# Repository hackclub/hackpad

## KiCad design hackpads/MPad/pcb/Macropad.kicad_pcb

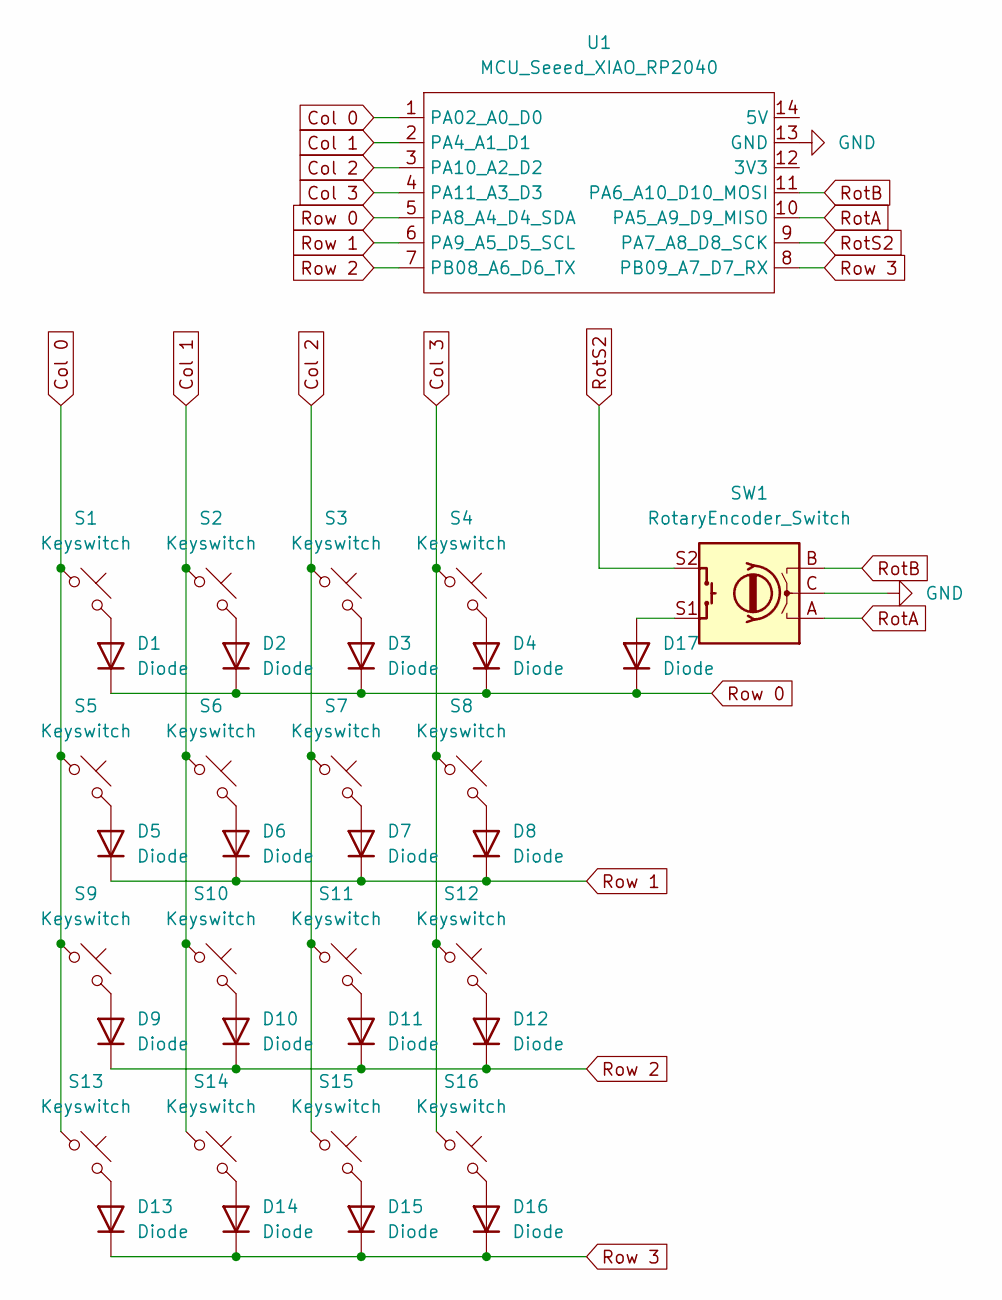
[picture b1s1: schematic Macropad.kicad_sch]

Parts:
D1, D2, D3, D4, D5, D6, D7, D8, D9, D10, D11, D12, D13, D14, D15, D16, D17: Diode; Diode_DO-35
S1, S2, S3, S4, S5, S6, S7, S8, S9, S10, S11, S12, S13, S14, S15, S16: Keyswitch; MX_PCB_1.00u
SW1: RotaryEncoder_Switch; RotaryEncoder_Alps_EC11E-Switch_Vertical_H20mm_CircularMoun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
U1: MCU_Seeed_XIAO_RP2040; Seeed_XIAO_RP2040

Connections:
Col 0: S1.1, S5.1, S9.1, S13.1, U1.1 (PA02_A0_D0)
Col 1: S2.1, S6.1, S10.1, S14.1, U1.2 (PA4_A1_D1)
Col 2: S3.1, S7.1, S11.1, S15.1, U1.3 (PA10_A2_D2)
Col 3: S4.1, S8.1, S12.1, S16.1, U1.4 (PA11_A3_D3)
GND: SW1.C, U1.13 (GND)
unnamed: D1.2 (A), S1.2
unnamed: D2.2 (A), S2.2
unnamed: D3.2 (A), S3.2
unnamed: D4.2 (A), S4.2
unnamed: D5.2 (A), S5.2
unnamed: D6.2 (A), S6.2
unnamed: D7.2 (A), S7.2
unnamed: D8.2 (A), S8.2
unnamed: D9.2 (A), S9.2
unnamed: D10.2 (A), S10.2
unnamed: D11.2 (A), S11.2
unnamed: D12.2 (A), S12.2
unnamed: D13.2 (A), S13.2
unnamed: D14.2 (A), S14.2
unnamed: D15.2 (A), S15.2
unnamed: D16.2 (A), S16.2
unnamed: D17.2 (A), SW1.S1
RotA: SW1.A, U1.10 (PA5_A9_D9_MISO)
RotB: SW1.B, U1.11 (PA6_A10_D10_MOSI)
RotS2: SW1.S2, U1.9 (PA7_A8_D8_SCK)
Row 0: D1.1 (K), D2.1 (K), D3.1 (K), D4.1 (K), D17.1 (K), U1.5 (PA8_A4_D4_SDA)
Row 1: D5.1 (K), D6.1 (K), D7.1 (K), D8.1 (K), U1.6 (PA9_A5_D5_SCL)
Row 2: D9.1 (K), D10.1 (K), D11.1 (K), D12.1 (K), U1.7 (PB08_A6_D6_TX)
Row 3: D13.1 (K), D14.1 (K), D15.1 (K), D16.1 (K), U1.8 (PB09_A7_D7_RX)

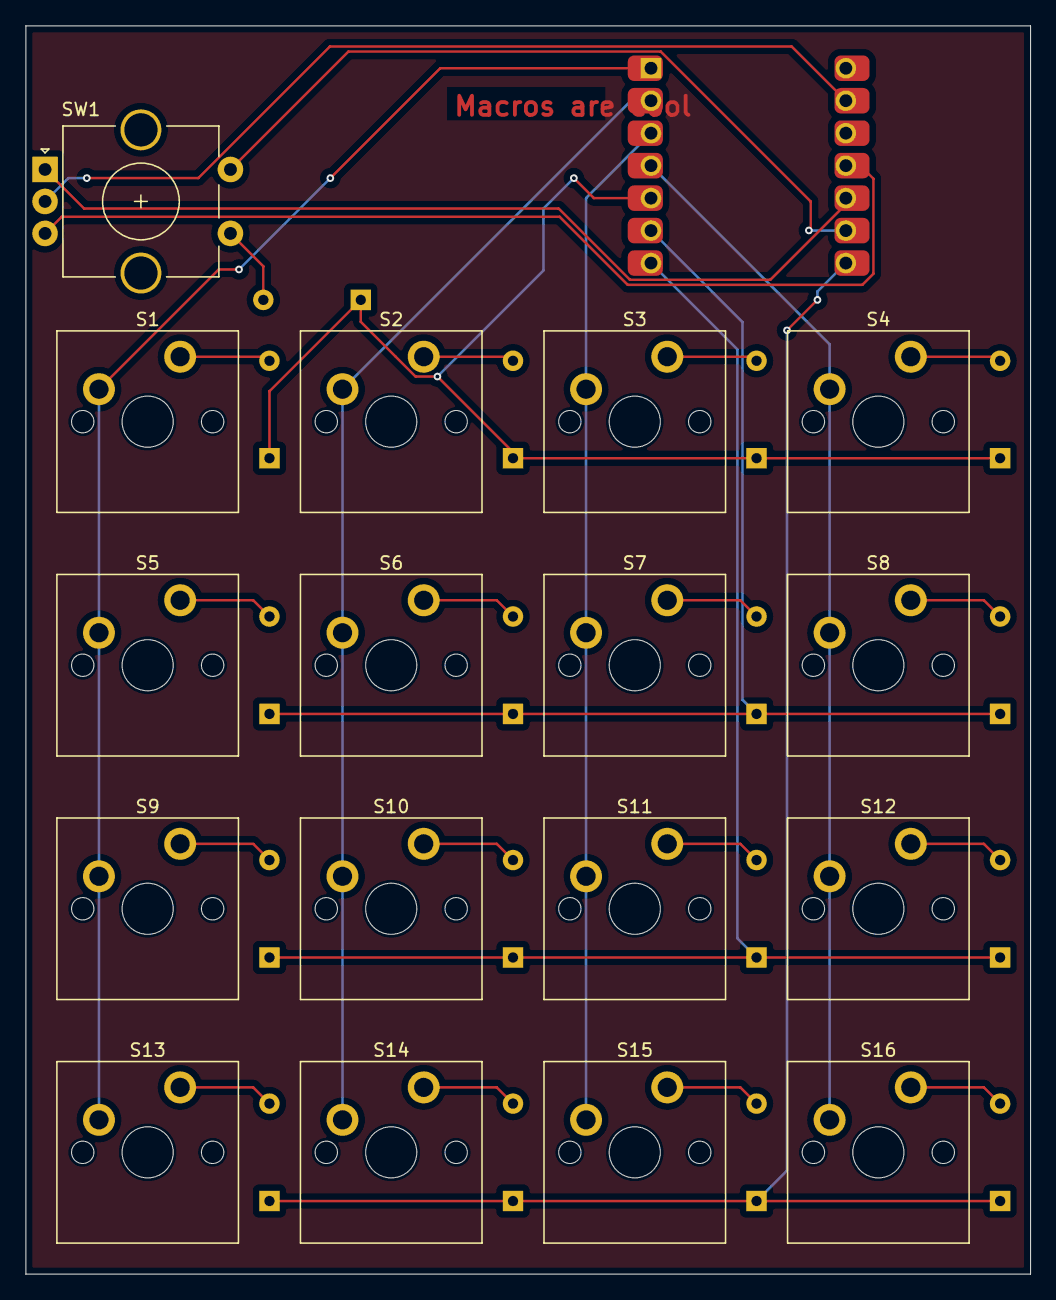
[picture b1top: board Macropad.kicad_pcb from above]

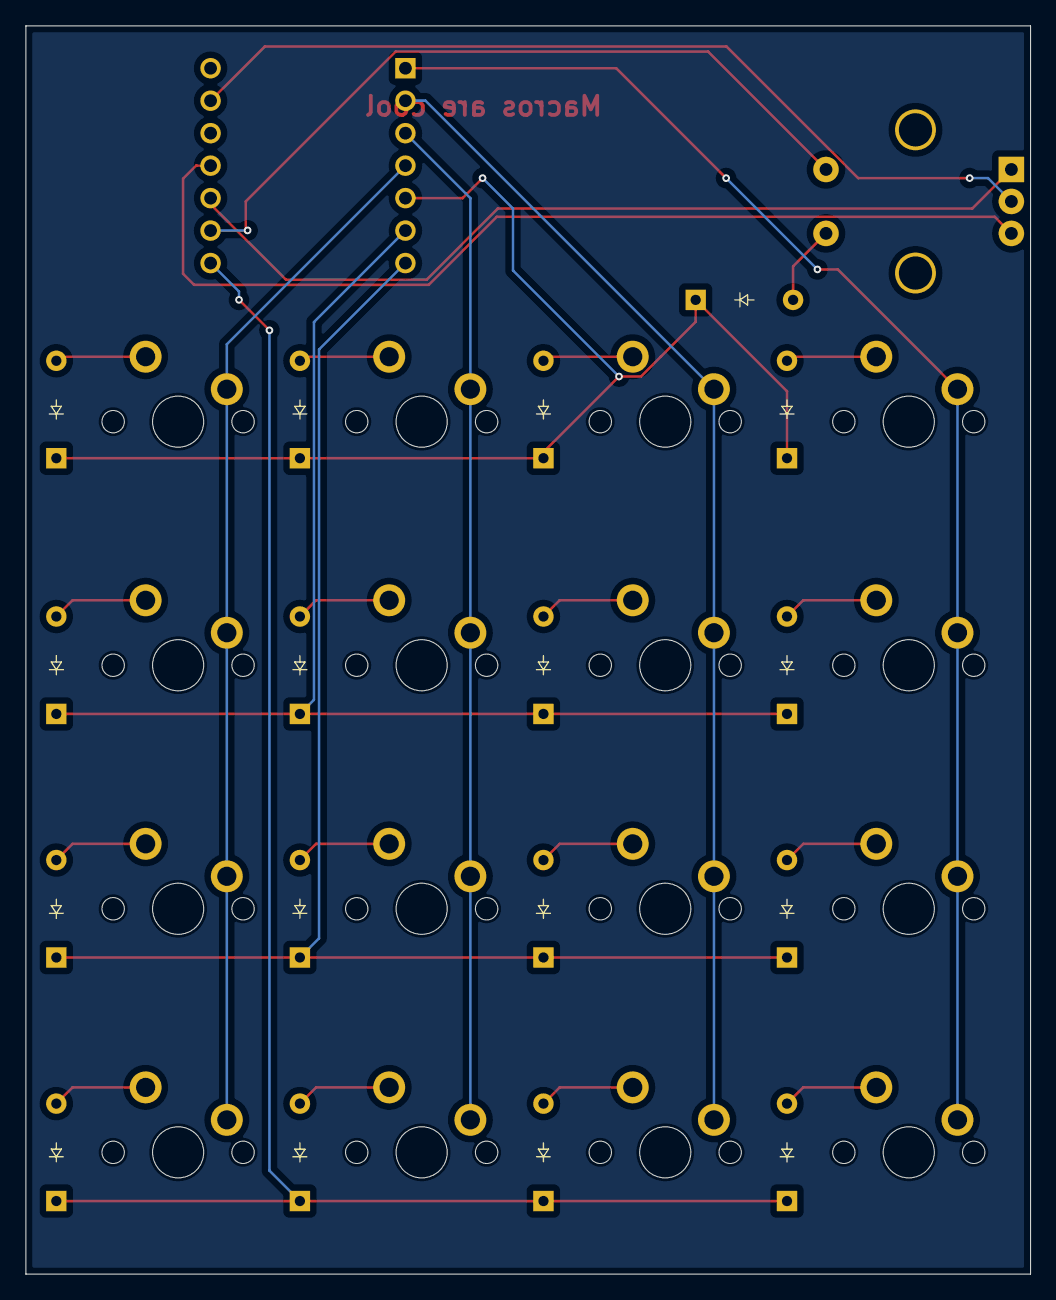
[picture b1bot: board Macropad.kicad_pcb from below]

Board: 2 copper layers, 78.6 x 97.6 mm, 35 parts (17 on the bottom side), 29 nets.

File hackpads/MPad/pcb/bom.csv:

Designator,Footprint,Quantity,Value,LCSC Part #
"D1, D10, D11, D12, D13, D14, D15, D16, D17, D2, D3, D4, D5, D6, D7, D8, D9",Diode_DO-35,17,Diode,
"S1, S10, S11, S12, S13, S14, S15, S16, S2, S3, S4, S5, S6, S7, S8, S9",MX_PCB_1.00u,16,Keyswitch,
SW1,RotaryEncoder_Alps_EC11E-Switch_Vertical_H20mm_CircularMountingHoles,1,RotaryEncoder_Switch,
U1,Seeed_XIAO_RP2040,1,MCU_Seeed_XIAO_RP2040,

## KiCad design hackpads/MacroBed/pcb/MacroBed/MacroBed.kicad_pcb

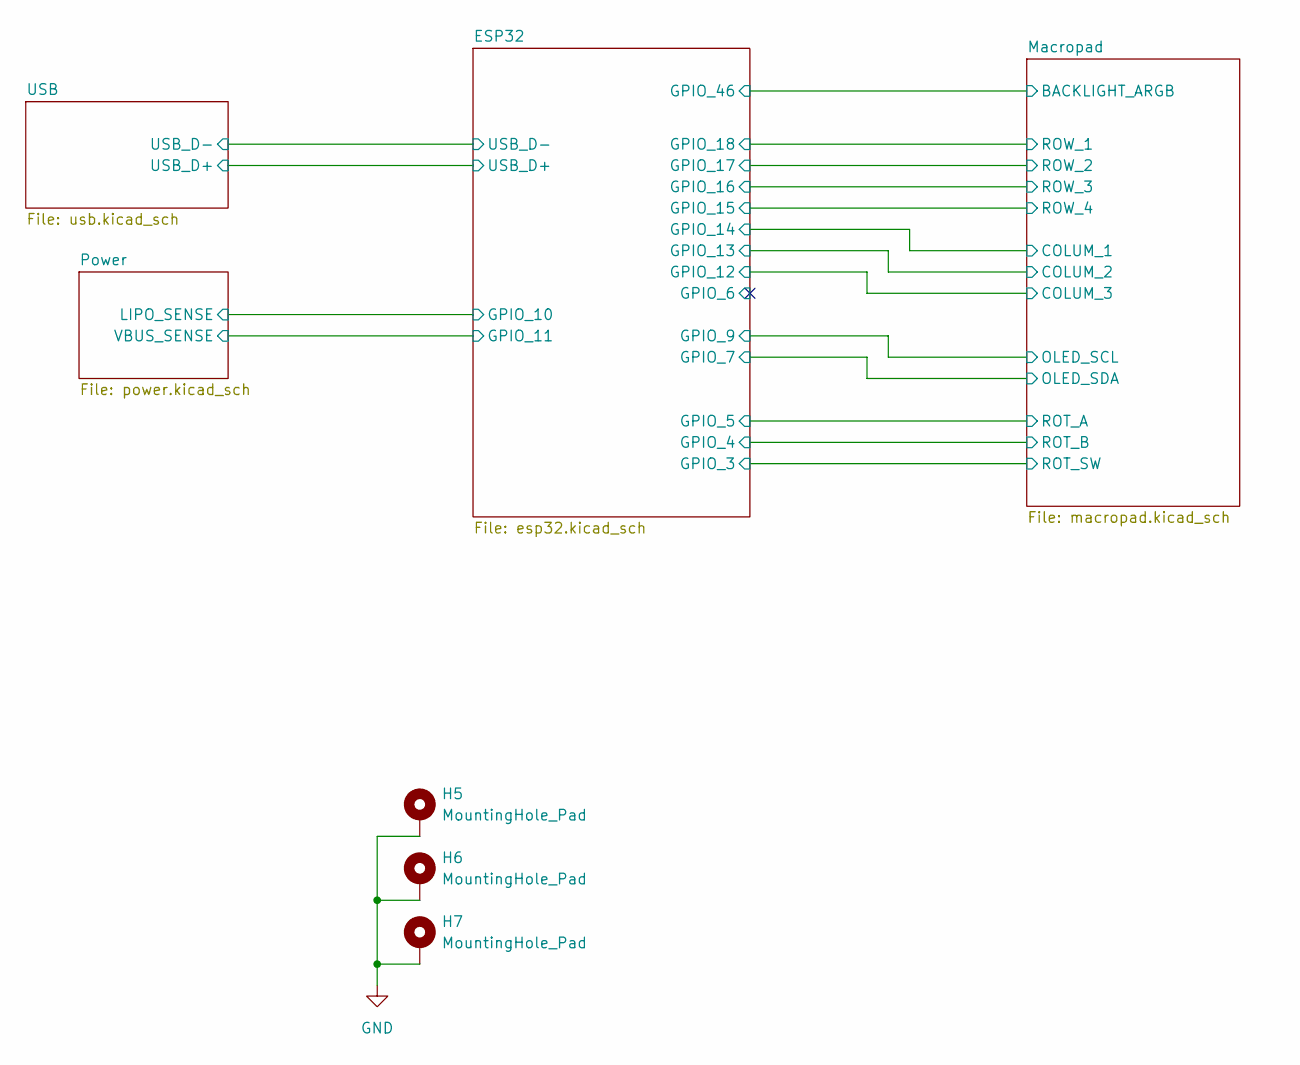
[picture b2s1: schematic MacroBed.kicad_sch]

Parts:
H5, H6, H7: MountingHole_Pad; MountingHole_3.2mm_M3_DIN965_Pad

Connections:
GND: H5.1, H6.1, H7.1; also elsewhere on the board

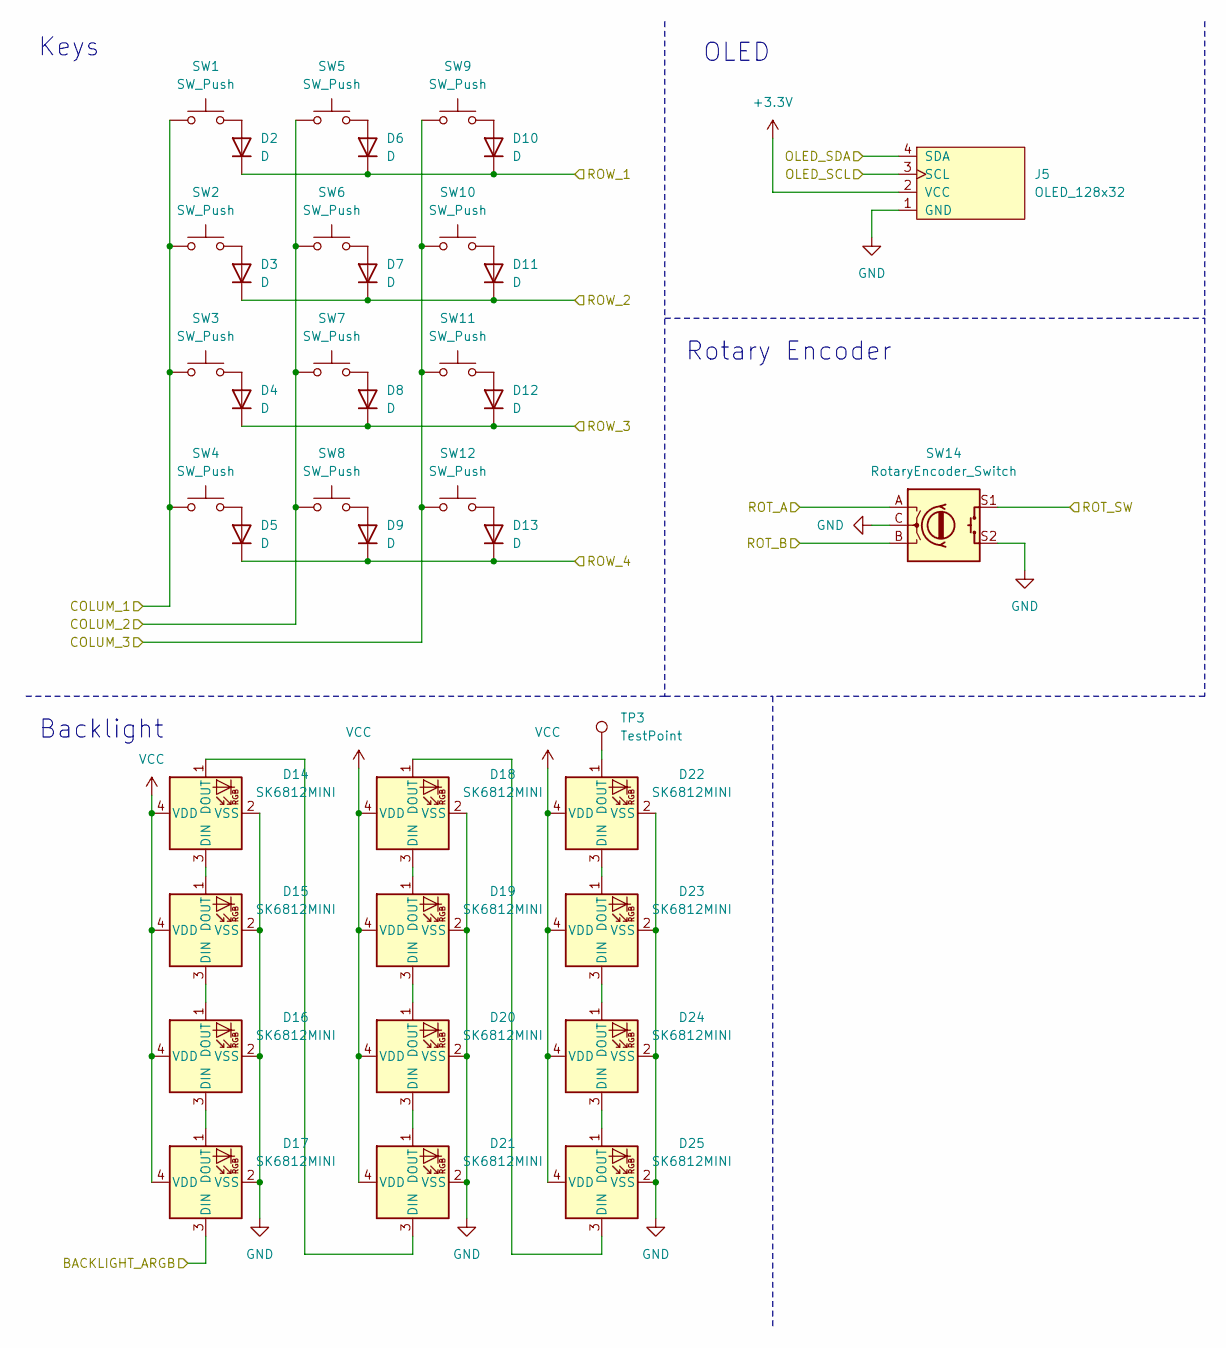
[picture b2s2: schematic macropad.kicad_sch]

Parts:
D2, D3, D4, D5, D6, D7, D8, D9, D10, D11, D12, D13: D; D_DO-35_SOD27_P7.62mm_Horizontal
D14, D15, D16, D17, D18, D19, D20, D21, D22, D23, D24, D25: SK6812MINI; SK6812-MINI-E
J5: OLED_128x32
SW1, SW2, SW3, SW4, SW5, SW6, SW7, SW8, SW9, SW10, SW11, SW12: SW_Push; SW_Cherry_MX_1.00u_PCB
SW14: RotaryEncoder_Switch; RotaryEncoder_Alps_EC11E-Switch_Vertical_H20mm_CircularMoun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
TP3: TestPoint; TestPoint_Pad_D1.5mm

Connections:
+3.3V: J5.2 (VCC); also elsewhere on the board
/ESP32/GPIO_3: SW14.S1; also elsewhere on the board
/ESP32/GPIO_4: SW14.B; also elsewhere on the board
/ESP32/GPIO_5: SW14.A; also elsewhere on the board
/ESP32/GPIO_7: J5.4 (SDA); also elsewhere on the board
/ESP32/GPIO_9: J5.3 (SCL); also elsewhere on the board
/ESP32/GPIO_12: SW9.1, SW10.1, SW11.1, SW12.1; also elsewhere on the board
/ESP32/GPIO_13: SW5.1, SW6.1, SW7.1, SW8.1; also elsewhere on the board
/ESP32/GPIO_14: SW1.1, SW2.1, SW3.1, SW4.1; also elsewhere on the board
/ESP32/GPIO_15: D5.1 (K), D9.1 (K), D13.1 (K); also elsewhere on the board
/ESP32/GPIO_16: D4.1 (K), D8.1 (K), D12.1 (K); also elsewhere on the board
/ESP32/GPIO_17: D3.1 (K), D7.1 (K), D11.1 (K); also elsewhere on the board
/ESP32/GPIO_18: D2.1 (K), D6.1 (K), D10.1 (K); also elsewhere on the board
/ESP32/GPIO_46: D17.3 (DIN); also elsewhere on the board
GND: D14.2 (VSS), D15.2 (VSS), D16.2 (VSS), D17.2 (VSS), D18.2 (VSS), D19.2 (VSS), D20.2 (VSS), D21.2 (VSS), D22.2 (VSS), D23.2 (VSS), D24.2 (VSS), D25.2 (VSS), J5.1 (GND), SW14.C, SW14.S2; also elsewhere on the board
unnamed: D2.2 (A), SW1.2
unnamed: D3.2 (A), SW2.2
unnamed: D4.2 (A), SW3.2
unnamed: D5.2 (A), SW4.2
unnamed: D6.2 (A), SW5.2
unnamed: D7.2 (A), SW6.2
unnamed: D8.2 (A), SW7.2
unnamed: D9.2 (A), SW8.2
unnamed: D10.2 (A), SW9.2
unnamed: D11.2 (A), SW10.2
unnamed: D12.2 (A), SW11.2
unnamed: D13.2 (A), SW12.2
unnamed: D14.3 (DIN), D15.1 (DOUT)
unnamed: D14.1 (DOUT), D21.3 (DIN)
unnamed: D15.3 (DIN), D16.1 (DOUT)
unnamed: D16.3 (DIN), D17.1 (DOUT)
unnamed: D18.3 (DIN), D19.1 (DOUT)
unnamed: D18.1 (DOUT), D25.3 (DIN)
unnamed: D19.3 (DIN), D20.1 (DOUT)
unnamed: D20.3 (DIN), D21.1 (DOUT)
unnamed: D22.3 (DIN), D23.1 (DOUT)
unnamed: D22.1 (DOUT), TP3.1
unnamed: D23.3 (DIN), D24.1 (DOUT)
unnamed: D24.3 (DIN), D25.1 (DOUT)
VCC: D14.4 (VDD), D15.4 (VDD), D16.4 (VDD), D17.4 (VDD), D18.4 (VDD), D19.4 (VDD), D20.4 (VDD), D21.4 (VDD), D22.4 (VDD), D23.4 (VDD), D24.4 (VDD), D25.4 (VDD); also elsewhere on the board

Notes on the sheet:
Backlight
Keys
OLED
Rotary Encoder

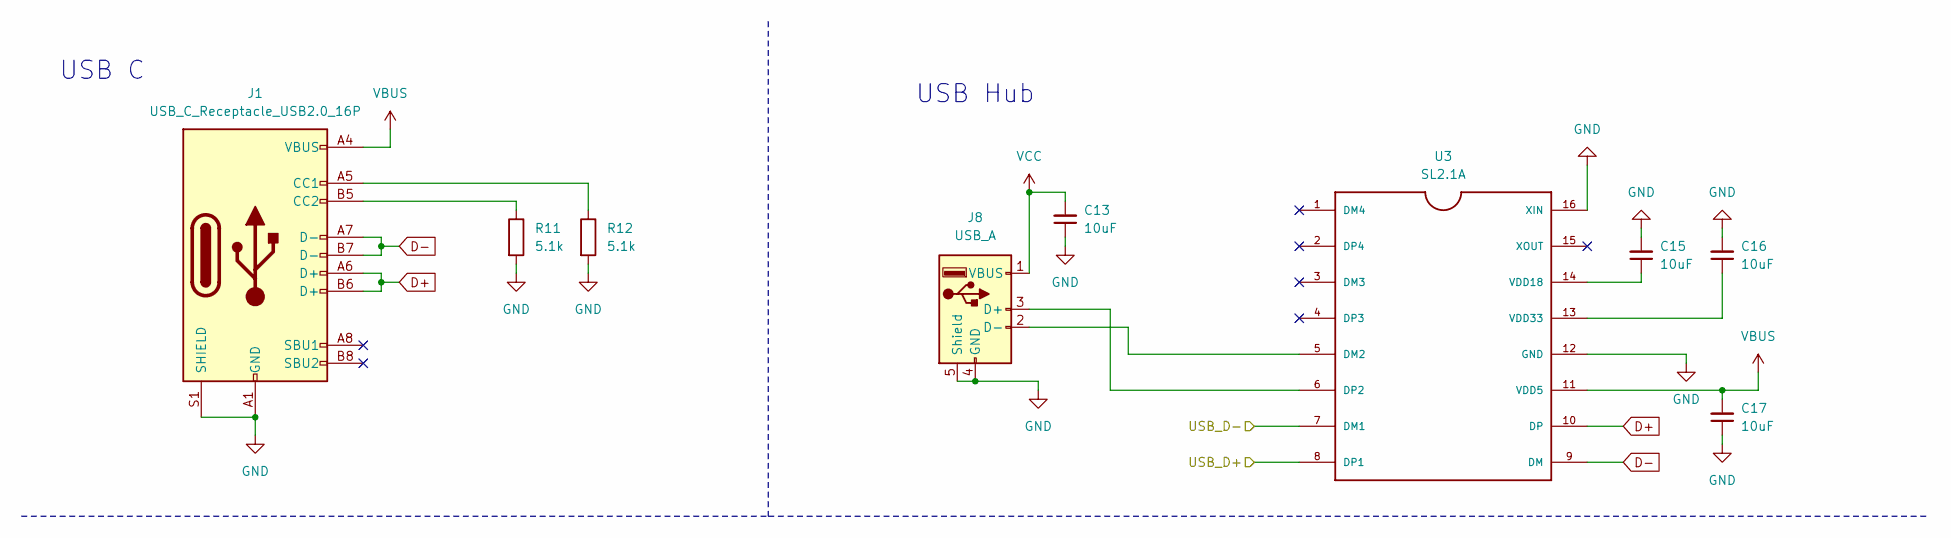
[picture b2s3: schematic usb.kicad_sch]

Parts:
C13, C15, C16, C17: 10uF; C_0805_2012Metric_Pad1.18x1.45mm_HandSolder
J1: USB_C_Receptacle_USB2.0_16P; USB_C_Receptacle_G-Switch_GT-USB-7010ASV
J8: USB_A; USB_A_CONNFLY_DS1095-WNR0
R11, R12: 5.1k; R_0805_2012Metric_Pad1.20x1.40mm_HandSolder
U3: SL2.1A; SO16

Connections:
/ESP32/USB_D+: U3.8 (DP1); also elsewhere on the board
/ESP32/USB_D-: U3.7 (DM1); also elsewhere on the board
D+: J1.A6 (D+), J1.B6 (D+), U3.10 (DP)
D-: J1.A7 (D-), J1.B7 (D-), U3.9 (DM)
GND: C13.1, C15.2, C16.2, C17.1, J1.A1 (GND), J1.A12 (GND), J1.B1 (GND), J1.B12 (GND), J1.S1 (SHIELD), J8.4 (GND), J8.5 (Shield), R11.2, R12.2, U3.12 (GND), U3.16 (XIN); also elsewhere on the board
unnamed: J1.A5 (CC1), R12.1
unnamed: J1.B5 (CC2), R11.1
unnamed: J8.3 (D+), U3.6 (DP2)
unnamed: J8.2 (D-), U3.5 (DM2)
unnamed: C15.1, U3.14 (VDD18)
unnamed: C16.1, U3.13 (VDD33)
VBUS: C17.2, J1.A4 (VBUS), J1.A9 (VBUS), J1.B4 (VBUS), J1.B9 (VBUS), U3.11 (VDD5); also elsewhere on the board
VCC: C13.2, J8.1 (VBUS); also elsewhere on the board

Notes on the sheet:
USB C
USB Hub

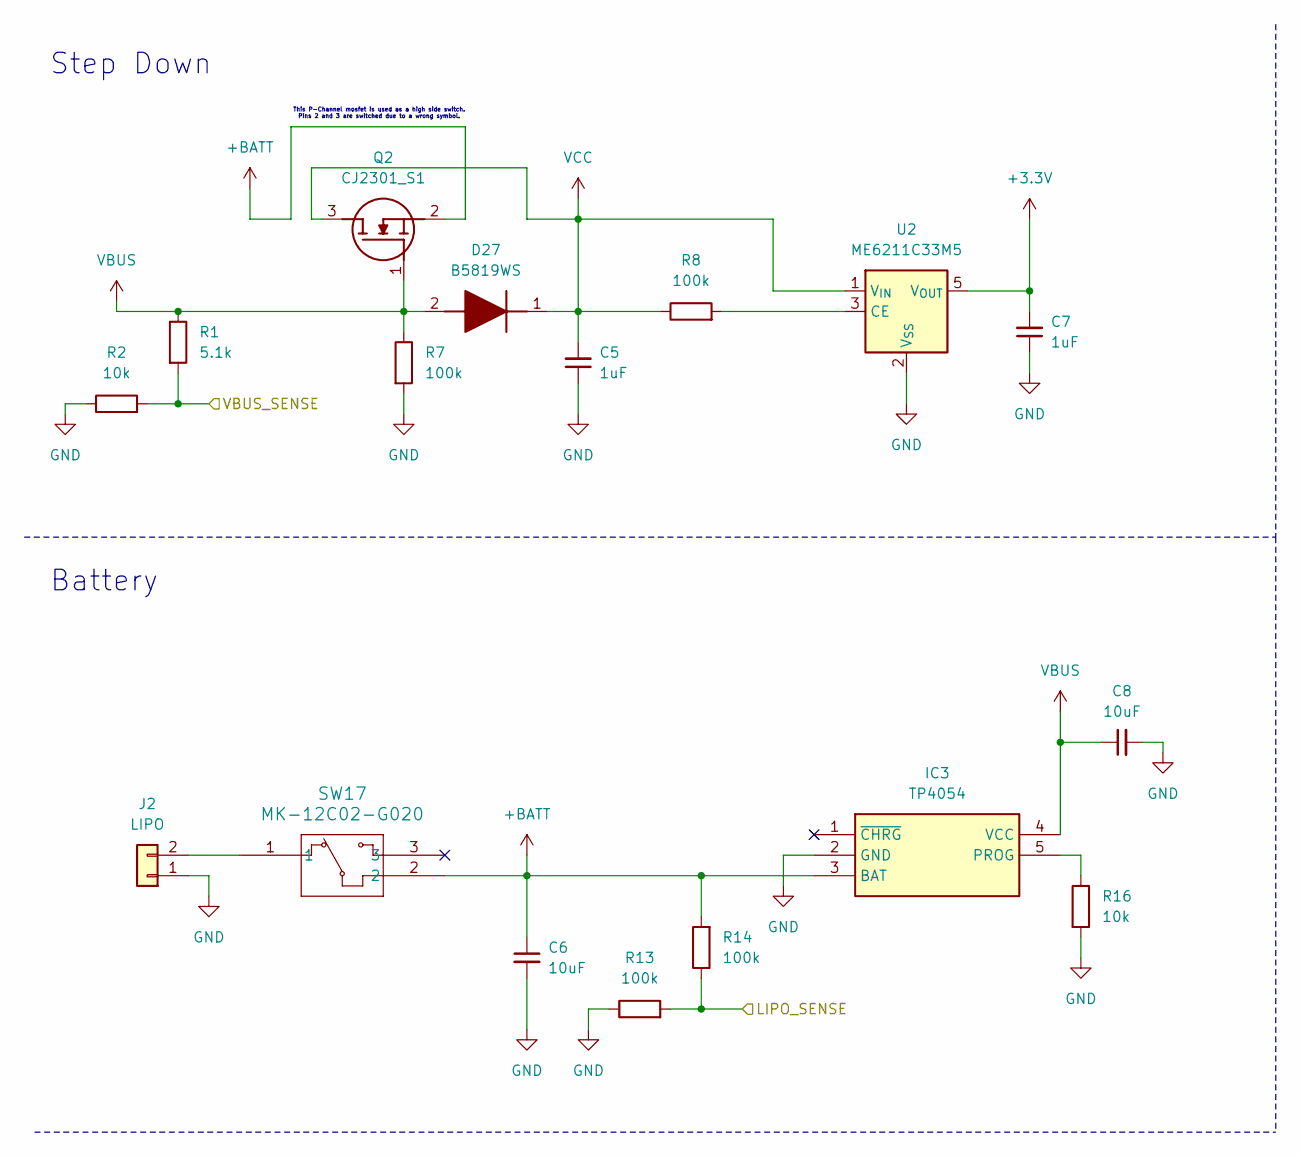
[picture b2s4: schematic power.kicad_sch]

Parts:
C5, C7: 1uF; C_0805_2012Metric_Pad1.18x1.45mm_HandSolder
C6, C8: 10uF; C_0805_2012Metric_Pad1.18x1.45mm_HandSolder
D27: B5819WS; C_0805_2012Metric_Pad1.18x1.45mm_HandSolder; Manufacturer_Part_Number B5819WS
IC3: TP4054; SOT95P280X100-5N; Manufacturer_Part_Number TP4054
J2: LIPO; JST_PH_B2B-PH-K_1x02_P2.00mm_Vertical
Q2: CJ2301_S1; SOT95P240X115-3N; Manufacturer_Part_Number CJ2301 S1
R1: 5.1k; R_0805_2012Metric_Pad1.20x1.40mm_HandSolder
R2, R16: 10k; R_0805_2012Metric_Pad1.20x1.40mm_HandSolder
R7, R8, R13, R14: 100k; R_0805_2012Metric_Pad1.20x1.40mm_HandSolder
SW17: MK-12C02-G020; MK-12C02-G020_GSW
U2: ME6211C33M5; SOT95P282X145-5N

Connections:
+3.3V: C7.2, U2.5 (V_{OUT}); also elsewhere on the board
+BATT: C6.1, IC3.3 (BAT), Q2.2 (S), R14.2, SW17.2
/ESP32/GPIO_10: R13.2, R14.1; also elsewhere on the board
/ESP32/GPIO_11: R1.2, R2.2; also elsewhere on the board
GND: C5.1, C6.2, C7.1, C8.2, IC3.2 (GND), J2.1, R2.1, R7.2, R13.1, R16.2, U2.2 (V_{SS}); also elsewhere on the board
unnamed: IC3.5 (PROG), R16.1
unnamed: J2.2, SW17.1
unnamed: R8.2, U2.3 (CE)
VBUS: C8.1, D27.2 (A), IC3.4 (VCC), Q2.1 (G), R1.1, R7.1; also elsewhere on the board
VCC: C5.2, D27.1 (K), Q2.3 (D), R8.1, U2.1 (V_{IN}); also elsewhere on the board

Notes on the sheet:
This P-Channel mosfet is used as a high side switch. Pins 2 and 3 are switched due to a wrong symbol.
Step Down
Battery

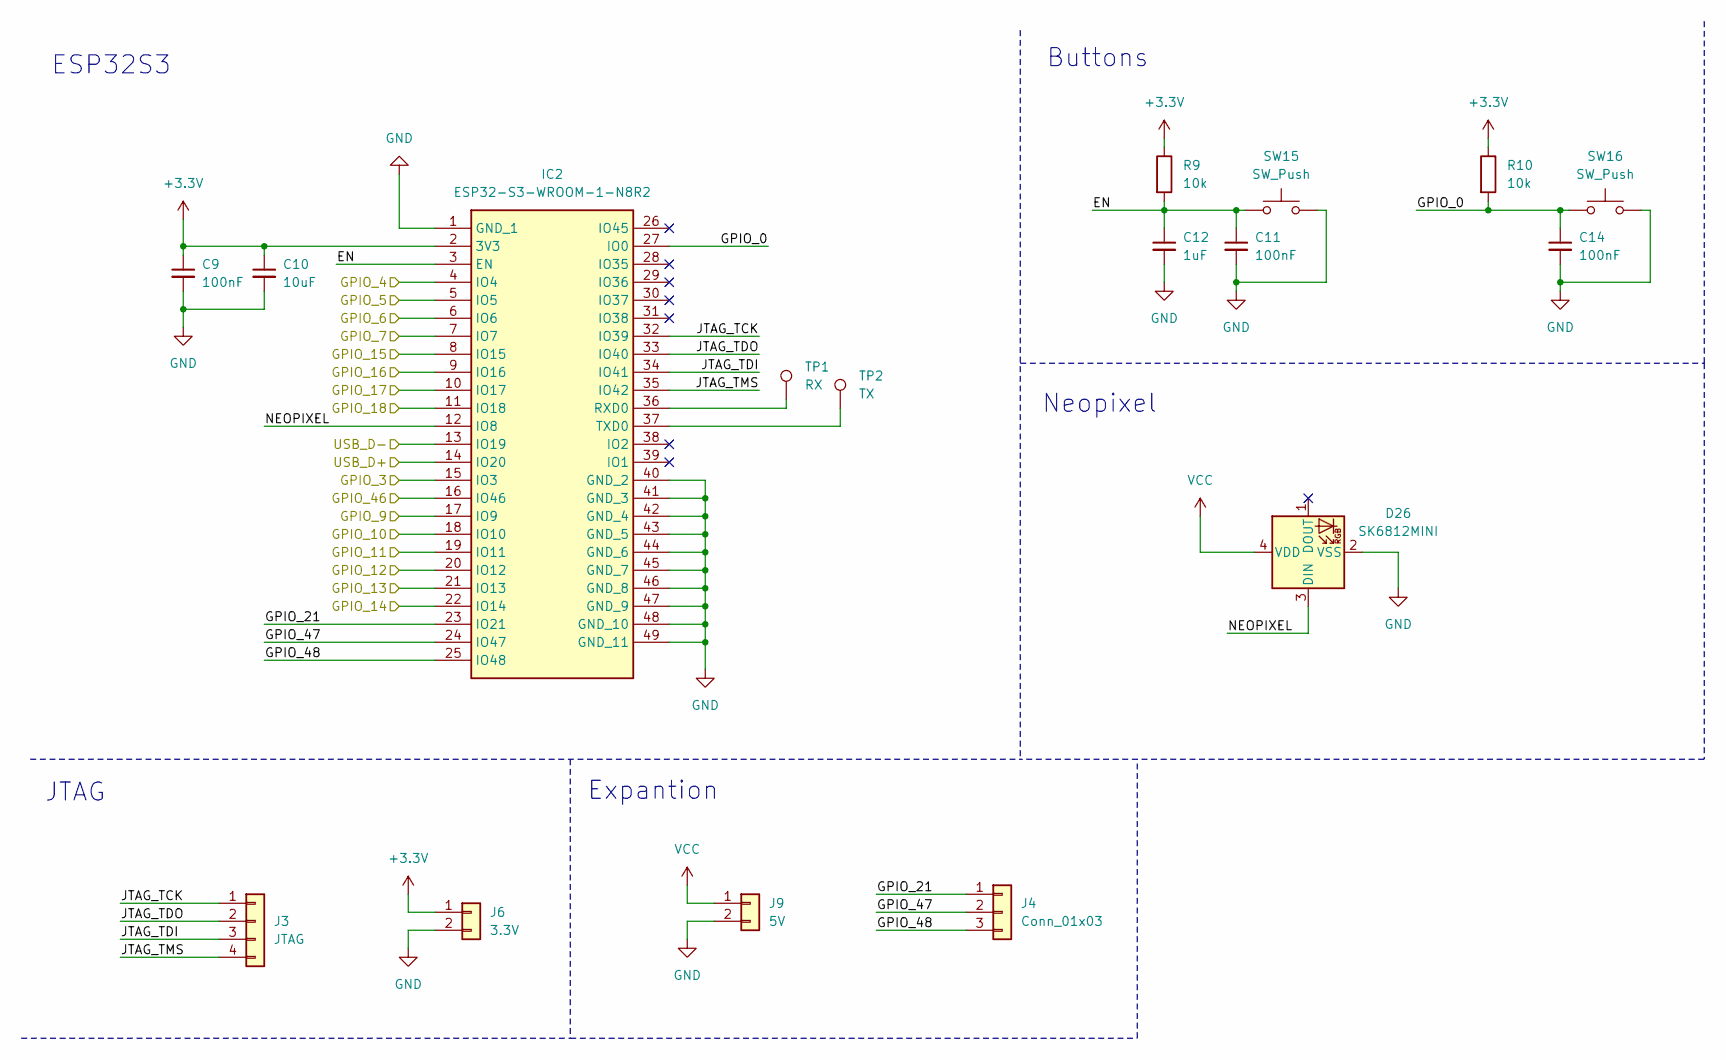
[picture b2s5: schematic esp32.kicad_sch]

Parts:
C9, C11, C14: 100nF; C_0805_2012Metric_Pad1.18x1.45mm_HandSolder
C10: 10uF; C_0805_2012Metric_Pad1.18x1.45mm_HandSolder
C12: 1uF; C_0805_2012Metric_Pad1.18x1.45mm_HandSolder
D26: SK6812MINI; SK6812-MINI-E
IC2: ESP32-S3-WROOM-1-N8R2; ESP32S3WROOM1N8R2; Manufacturer_Part_Number ESP32-S3-WROOM-1-N8R2; Mouser Part Number 356-ESP32-S3WRM1N8R2
J3: JTAG; PinHeader_1x04_P1.00mm_Vertical
J4: Conn_01x03; PinHeader_1x03_P2.54mm_Vertical
J6: 3.3V; PinHeader_1x02_P2.54mm_Vertical
J9: 5V; PinHeader_1x02_P2.54mm_Vertical
R9, R10: 10k; R_0805_2012Metric_Pad1.20x1.40mm_HandSolder
SW15, SW16: SW_Push; SW_Push_SPST_NO_Alps_SKRK
TP1: RX; TestPoint_Pad_D1.5mm
TP2: TX; TestPoint_Pad_D1.5mm

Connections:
+3.3V: C9.1, C10.1, IC2.2 (3V3), J6.1, R9.1, R10.1; also elsewhere on the board
/ESP32/EN: C11.1, C12.1, IC2.3 (EN), R9.2, SW15.1
/ESP32/GPIO_0: C14.1, IC2.27 (IO0), R10.2, SW16.1
/ESP32/GPIO_3: IC2.15 (IO3); also elsewhere on the board
/ESP32/GPIO_4: IC2.4 (IO4); also elsewhere on the board
/ESP32/GPIO_5: IC2.5 (IO5); also elsewhere on the board
/ESP32/GPIO_6: IC2.6 (IO6)
/ESP32/GPIO_7: IC2.7 (IO7); also elsewhere on the board
/ESP32/GPIO_9: IC2.17 (IO9); also elsewhere on the board
/ESP32/GPIO_10: IC2.18 (IO10); also elsewhere on the board
/ESP32/GPIO_11: IC2.19 (IO11); also elsewhere on the board
/ESP32/GPIO_12: IC2.20 (IO12); also elsewhere on the board
/ESP32/GPIO_13: IC2.21 (IO13); also elsewhere on the board
/ESP32/GPIO_14: IC2.22 (IO14); also elsewhere on the board
/ESP32/GPIO_15: IC2.8 (IO15); also elsewhere on the board
/ESP32/GPIO_16: IC2.9 (IO16); also elsewhere on the board
/ESP32/GPIO_17: IC2.10 (IO17); also elsewhere on the board
/ESP32/GPIO_18: IC2.11 (IO18); also elsewhere on the board
/ESP32/GPIO_21: IC2.23 (IO21), J4.1
/ESP32/GPIO_46: IC2.16 (IO46); also elsewhere on the board
/ESP32/GPIO_47: IC2.24 (IO47), J4.2
/ESP32/GPIO_48: IC2.25 (IO48), J4.3
/ESP32/JTAG_TCK: IC2.32 (IO39), J3.1
/ESP32/JTAG_TDI: IC2.34 (IO41), J3.3
/ESP32/JTAG_TDO: IC2.33 (IO40), J3.2
/ESP32/JTAG_TMS: IC2.35 (IO42), J3.4
/ESP32/NEOPIXEL: D26.3 (DIN), IC2.12 (IO8)
/ESP32/USB_D+: IC2.14 (IO20); also elsewhere on the board
/ESP32/USB_D-: IC2.13 (IO19); also elsewhere on the board
GND: C9.2, C10.2, C11.2, C12.2, C14.2, D26.2 (VSS), IC2.1 (GND_1), IC2.40 (GND_2), IC2.41 (GND_3), IC2.42 (GND_4), IC2.43 (GND_5), IC2.44 (GND_6), IC2.45 (GND_7), IC2.46 (GND_8), IC2.47 (GND_9), IC2.48 (GND_10), IC2.49 (GND_11), J6.2, J9.2, SW15.2, SW16.2; also elsewhere on the board
unnamed: IC2.36 (RXD0), TP1.1
unnamed: IC2.37 (TXD0), TP2.1
VCC: D26.4 (VDD), J9.1; also elsewhere on the board

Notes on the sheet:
JTAG
Neopixel
ESP32S3
Buttons
Expantion

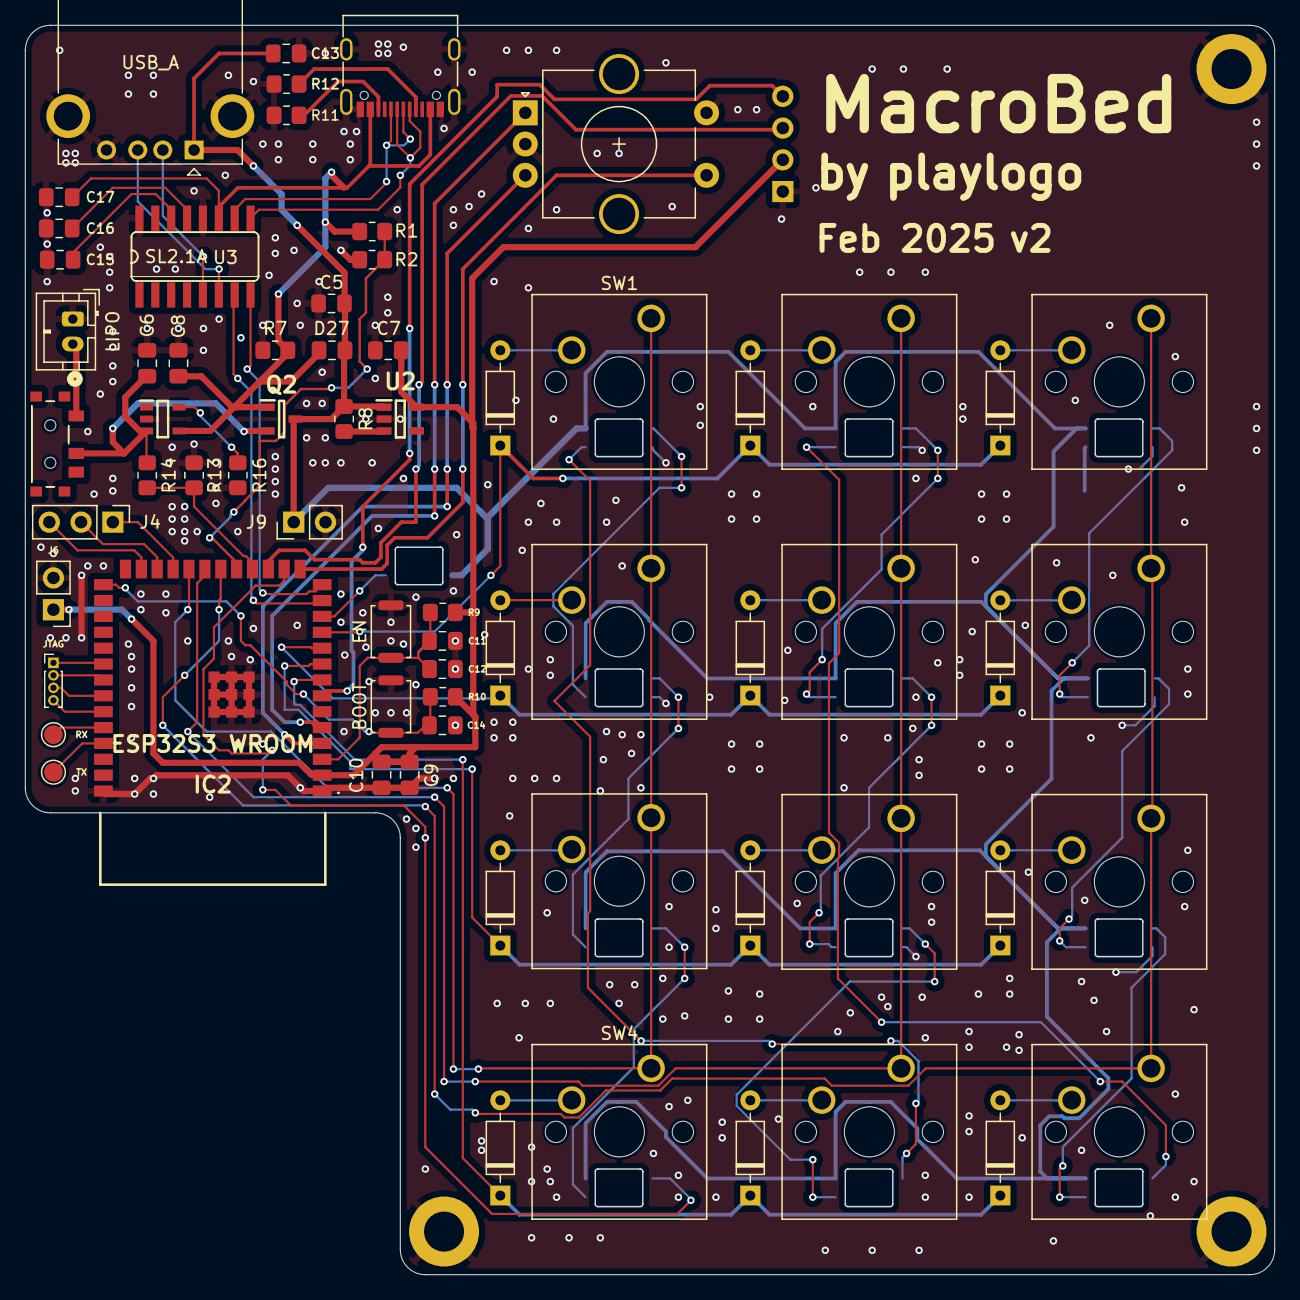
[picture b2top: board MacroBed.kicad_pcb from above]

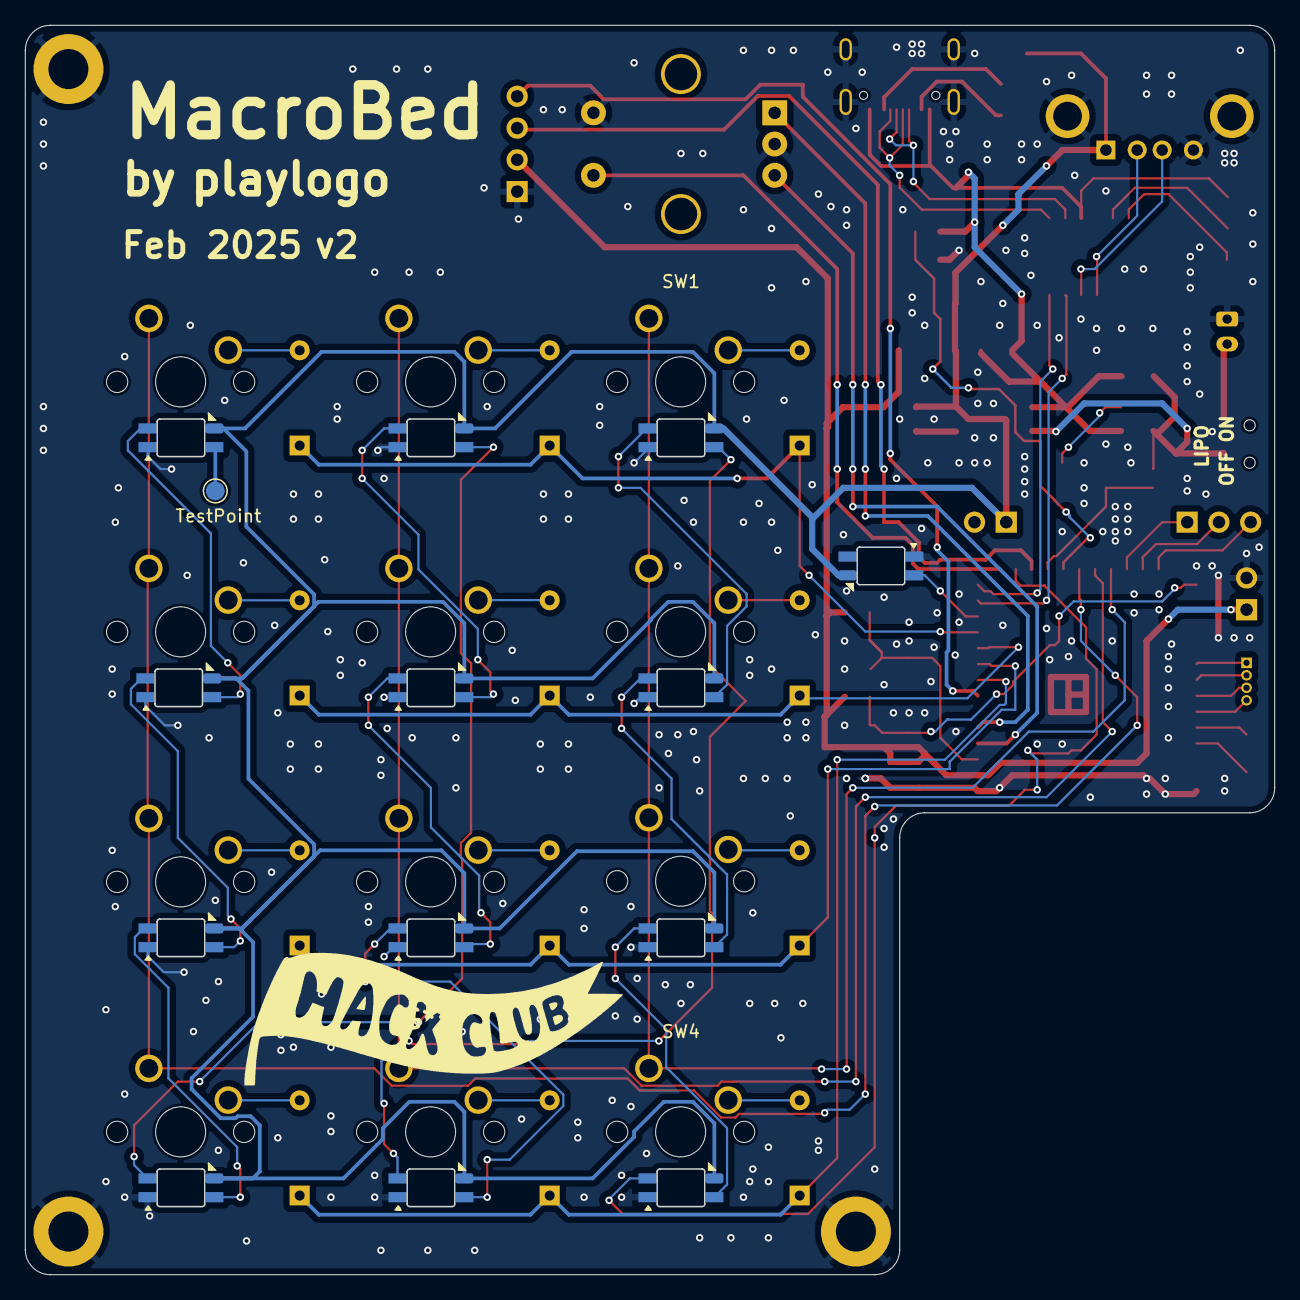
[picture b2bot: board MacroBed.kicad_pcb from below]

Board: 2 copper layers, 99.9 x 99.9 mm, 85 parts (14 on the bottom side), 69 nets.

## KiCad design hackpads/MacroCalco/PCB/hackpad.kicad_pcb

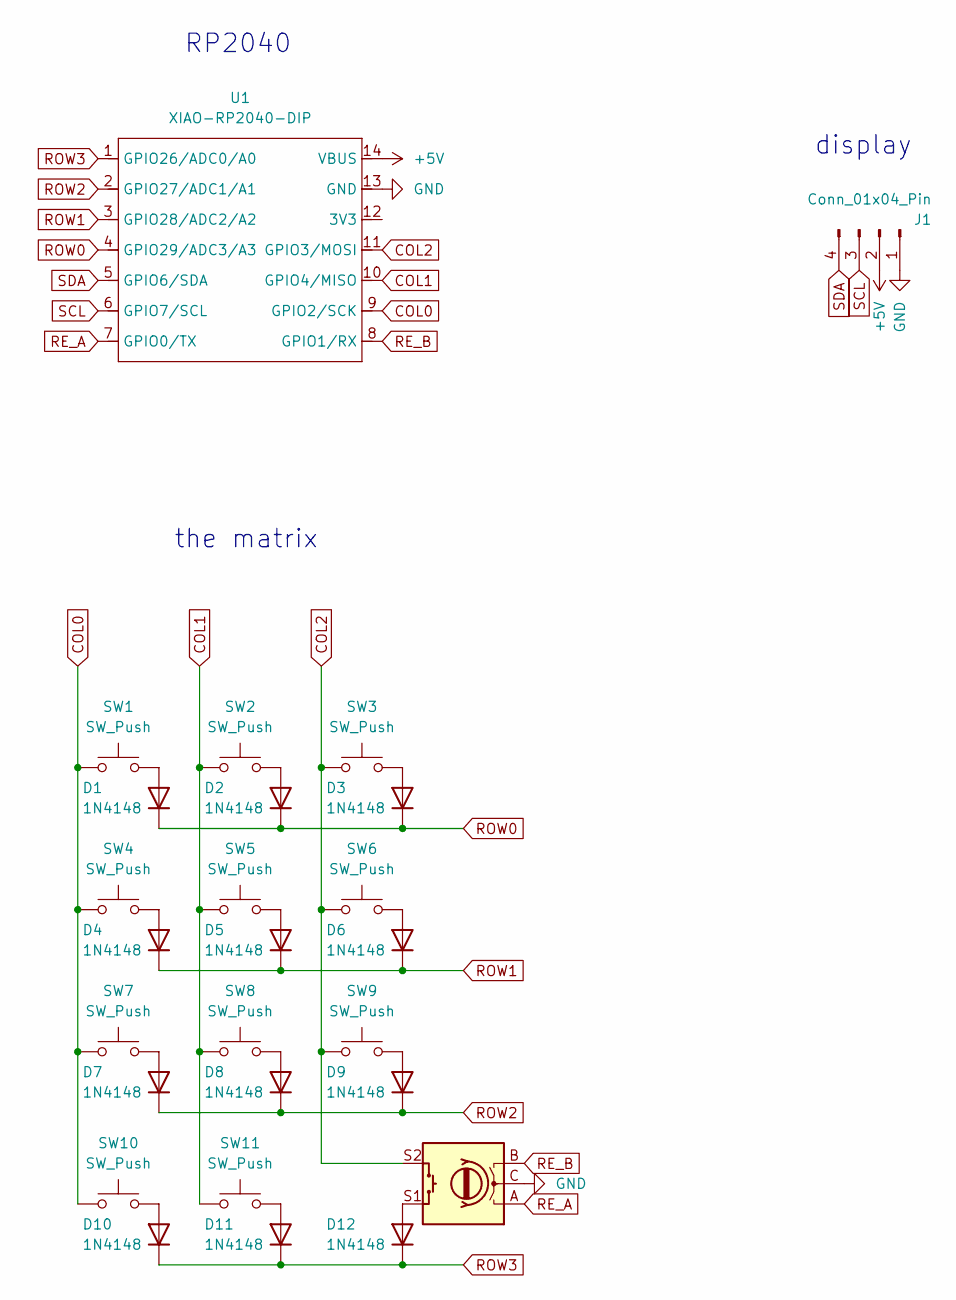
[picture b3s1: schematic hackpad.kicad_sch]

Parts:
D1, D2, D3, D4, D5, D6, D7, D8, D9, D10, D11, D12: 1N4148; D_DO-35_SOD27_P7.62mm_Horizontal
J1: Conn_01x04_Pin; SSD1306-0.91-OLED-4pin-128x32
SW1, SW2, SW3, SW4, SW5, SW6, SW7, SW8, SW9, SW10, SW11: SW_Push; SW_Cherry_MX_1.00u_PCB_3d
SW13: RotaryEncoder_Switch; RotaryEncoder_Alps_EC11E-Switch_Vertical_H20mm_CircularMoun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
U1: XIAO-RP2040-DIP

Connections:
+5V: J1.2, U1.14 (VBUS)
COL0: SW1.2, SW4.2, SW7.2, SW10.2, U1.9 (GPIO2/SCK)
COL1: SW2.2, SW5.2, SW8.2, SW11.2, U1.10 (GPIO4/MISO)
COL2: SW3.2, SW6.2, SW9.2, SW13.S2, U1.11 (GPIO3/MOSI)
GND: J1.1, SW13.C, U1.13 (GND)
unnamed: D1.2 (A), SW1.1
unnamed: D2.2 (A), SW2.1
unnamed: D3.2 (A), SW3.1
unnamed: D4.2 (A), SW4.1
unnamed: D5.2 (A), SW5.1
unnamed: D6.2 (A), SW6.1
unnamed: D7.2 (A), SW7.1
unnamed: D8.2 (A), SW8.1
unnamed: D9.2 (A), SW9.1
unnamed: D10.2 (A), SW10.1
unnamed: D11.2 (A), SW11.1
unnamed: D12.2 (A), SW13.S1
RE_A: SW13.A, U1.7 (GPIO0/TX)
RE_B: SW13.B, U1.8 (GPIO1/RX)
ROW0: D1.1 (K), D2.1 (K), D3.1 (K), U1.4 (GPIO29/ADC3/A3)
ROW1: D4.1 (K), D5.1 (K), D6.1 (K), U1.3 (GPIO28/ADC2/A2)
ROW2: D7.1 (K), D8.1 (K), D9.1 (K), U1.2 (GPIO27/ADC1/A1)
ROW3: D10.1 (K), D11.1 (K), D12.1 (K), U1.1 (GPIO26/ADC0/A0)
SCL: J1.3, U1.6 (GPIO7/SCL)
SDA: J1.4, U1.5 (GPIO6/SDA)

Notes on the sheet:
RP2040
display
the matrix
